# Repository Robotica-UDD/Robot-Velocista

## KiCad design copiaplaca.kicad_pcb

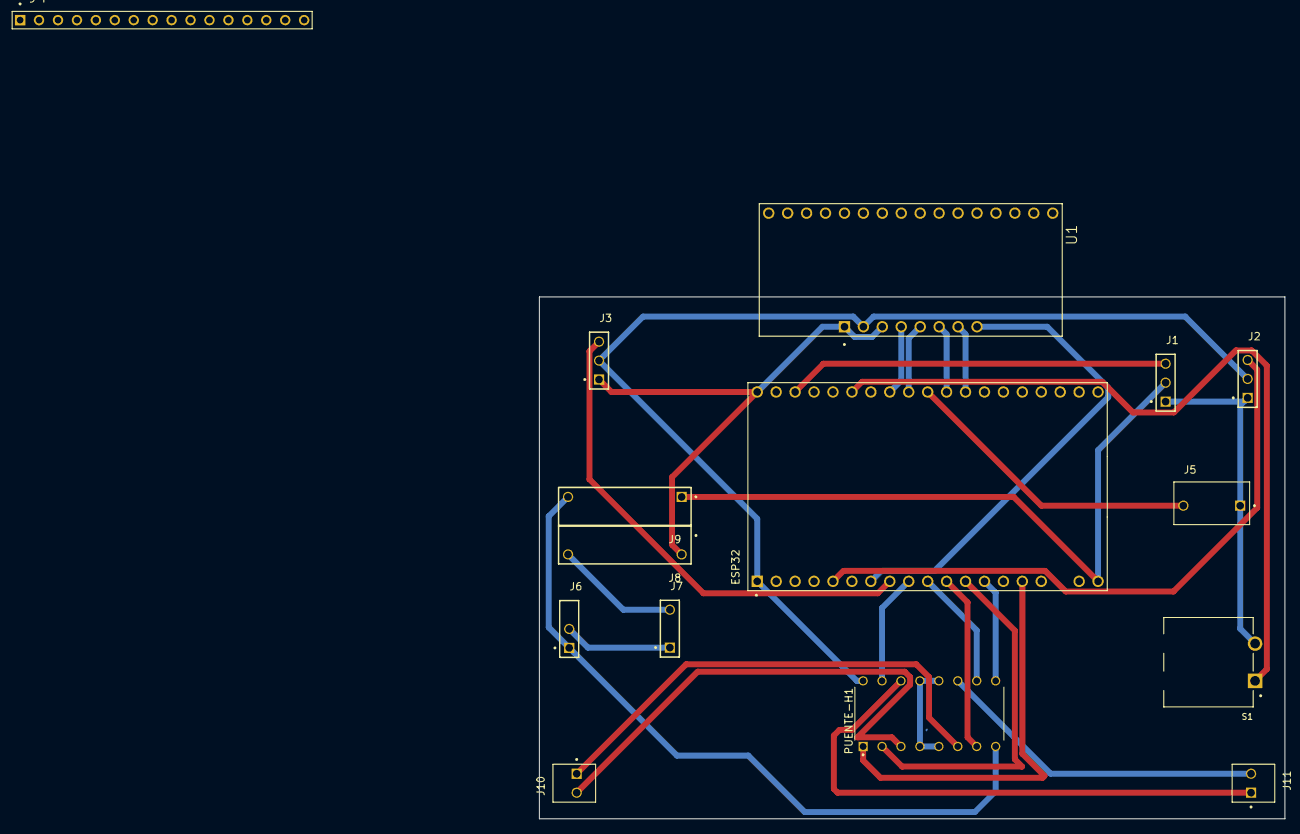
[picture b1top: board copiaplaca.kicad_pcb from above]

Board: 2 copper layers, 100.0 x 70.0 mm, 15 parts (0 on the bottom side), 41 nets.

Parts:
ESP32: ESP32-DEVKITC-32U; MODULE_ESP32-DEVKITC-32U
J1: ESC; SAMTEC_TSW-101-07-T-T
J2: LATERAL DERECHO; SAMTEC_TSW-101-07-T-T
J3: LATERAL IZQUIERDO; SAMTEC_TSW-101-07-T-T
J4: CONECTORES QTR; TE_6-146455-6
J5: BUZZER; TE_640456-4
J6: SWITCH; SAMTEC_TSW-101-07-T-T
J7: BATERIA; SAMTEC_TSW-101-07-T-T
J8, J9: R_V; SAMTEC_TSW-107-09-G-D-003
J10: Motor1; TE_640456-2
J11: Motor2; TE_640456-2
PUENTE-H1: L293D; DIP880W50P254L2000H510Q16
S1: BOTON; SW_VS-1213-67-160GF
U1: MUX 16X1; MODULE_BOB-09056

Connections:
3.3V: ESP32.1 (3V3), J2.02, J3.02, PUENTE-H1.16 (VSS), U1.JP3-2 (VCC)
5V: ESP32.19 (EXT_5V), J1.02, J9.01
7.4V_BATERIA: J6.01, J6.02, J7.01, J9.13, PUENTE-H1.8 (VS)
A0: J4.1, U1.JP1-1 (C0)
A1: J4.2, U1.JP1-2 (C1)
A2: J4.3, U1.JP1-3 (C2)
A3: J4.4, U1.JP1-4 (C3)
A4: J4.5, U1.JP1-5 (C4)
A5: J4.6, U1.JP1-6 (C5)
A6: J4.7, U1.JP1-7 (C6)
A7: J4.8, U1.JP1-8 (C7)
A8: J4.9, U1.JP1-9 (C8)
A9: J4.10, U1.JP1-10 (C9)
A10: J4.11, U1.JP1-11 (C10)
A11: J4.12, U1.JP1-12 (C11)
A12: J4.13, U1.JP1-13 (C12)
A13: J4.14, U1.JP1-14 (C13)
A14: J4.15, U1.JP1-15 (C14)
A15: J4.16, U1.JP1-16 (C15)
BOTON: ESP32.33 (IO21), S1.1
BUZZER: ESP32.29 (IO5), J5.4
GND: ESP32.38 (GND3), J1.01, J2.01, J3.01, J5.1, J8.02, PUENTE-H1.4 (GND), PUENTE-H1.5 (GND), PUENTE-H1.12 (GND), PUENTE-H1.13 (GND), S1.2, U1.JP3-1 (GND), U1.JP3-3 (EN)
GND_BATERIA: J7.03, J8.14
INA-1: ESP32.12 (IO14), PUENTE-H1.2 (INPUT1)
INA-2: ESP32.11 (IO27), PUENTE-H1.7 (INPUT2)
INB-1: ESP32.10 (IO26), PUENTE-H1.10 (INPUT3)
INB-2: ESP32.9 (IO25), PUENTE-H1.15 (INPUT4)
M1+: J10.2, PUENTE-H1.3 (OUTPUT1)
M1-: J10.1, PUENTE-H1.6 (OUTPUT2)
M2+: J11.2, PUENTE-H1.11 (OUTPUT3)
M2-: J11.1, PUENTE-H1.14 (OUTPUT4)
MUX-A: ESP32.7 (IO32), U1.JP3-8 (COM)
PWM-A: ESP32.15 (IO13), PUENTE-H1.1 (ENABLE1)
PWM-B: ESP32.13 (IO12), PUENTE-H1.9 (ENABLE2)
QTRD: ESP32.5 (IO34), J2.03
QTRI: ESP32.8 (IO33), J3.03
S0: ESP32.31 (IO19), U1.JP3-4 (S0)
S1: ESP32.30 (IO18), U1.JP3-5 (S1)
S2: ESP32.28 (IO17), U1.JP3-6 (S2)
S3: ESP32.27 (IO16), U1.JP3-7 (S3)
S_ESC: ESP32.36 (IO22), J1.03

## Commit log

2024-12-18 Codigo Buzzer
2024-12-18 Codigo_Push_Botton
2025-01-06 QTR15A-FUNCIONANDO
2025-01-06 Motores_funcionando
2025-01-10 Create Codigo laterales contando
